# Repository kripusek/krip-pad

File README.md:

# krip-pad
This is my macro pad madwe mainly for playing osumania type games

## Features
- A 0.91 inch OLED display
- 4 keys
- An opening to see the screen, xiao rp2040 and the oled

## tolerances
should be around 0.4mm

## WIP picture of the hack pad

(yes I have a really cool mousepad)

## PCB
Here are pictures of my pcb:

| **Schematic** | **PCB** |
|---------------|---------|
|||

## CAD
I designed it using autodesk fusion

Everything fits together with 5 m3 screws and bolts

## Firmware

I wrote the firmware using qmk.

## Notes
If you want to change the mapped you can use via with the included via.json file which you can find in the firmware folder https://usevia.app/

Making this pad was fun, I got to learn qmk fusion and kicad which I can use fluently now, fusion and qmk not so much.

I have used https://github.com/hackclub/hackpad/blob/main/hackpads/cyaopad/README.md as a template for my readme

I have used https://github.com/dancarroll/qmk-bongo for the bongo animations
I have also used ai for explaining what does what in qmk, afterwards I have written the code myself and ai has helped me debug it.

## BOM
- 1 SEEEDUINO XIAO RP2040
- 4x any switch mx style
- 4x 1N4148 diodes
- 1x default 32x128 with GND-VCC-SCL-SDA pin order
- 5x same screws as orpheuspad and corresponding nuts

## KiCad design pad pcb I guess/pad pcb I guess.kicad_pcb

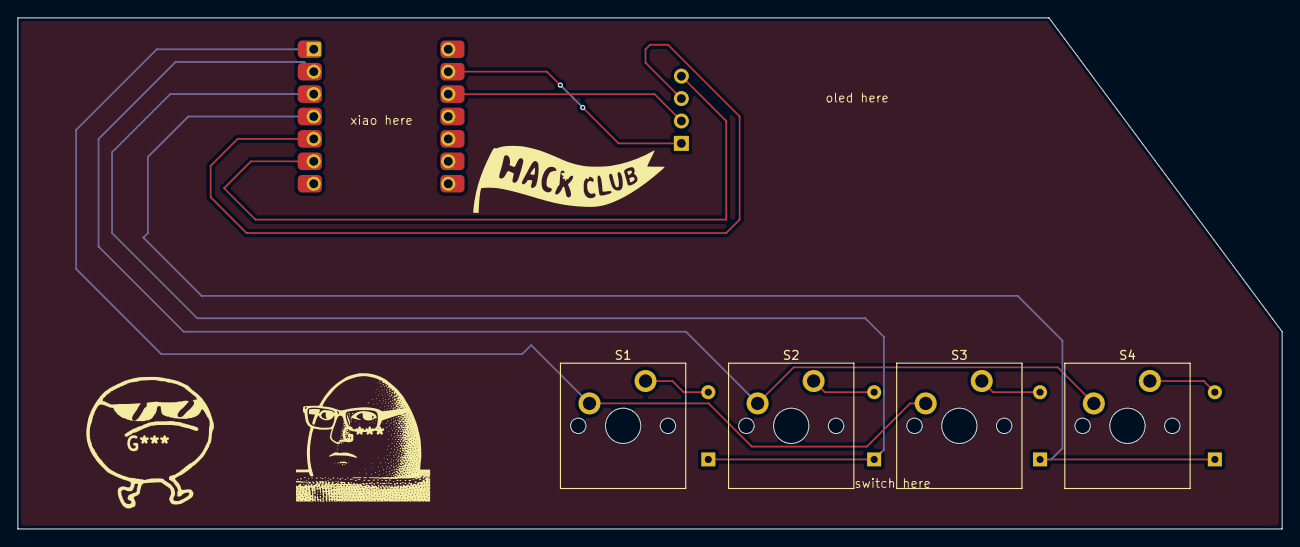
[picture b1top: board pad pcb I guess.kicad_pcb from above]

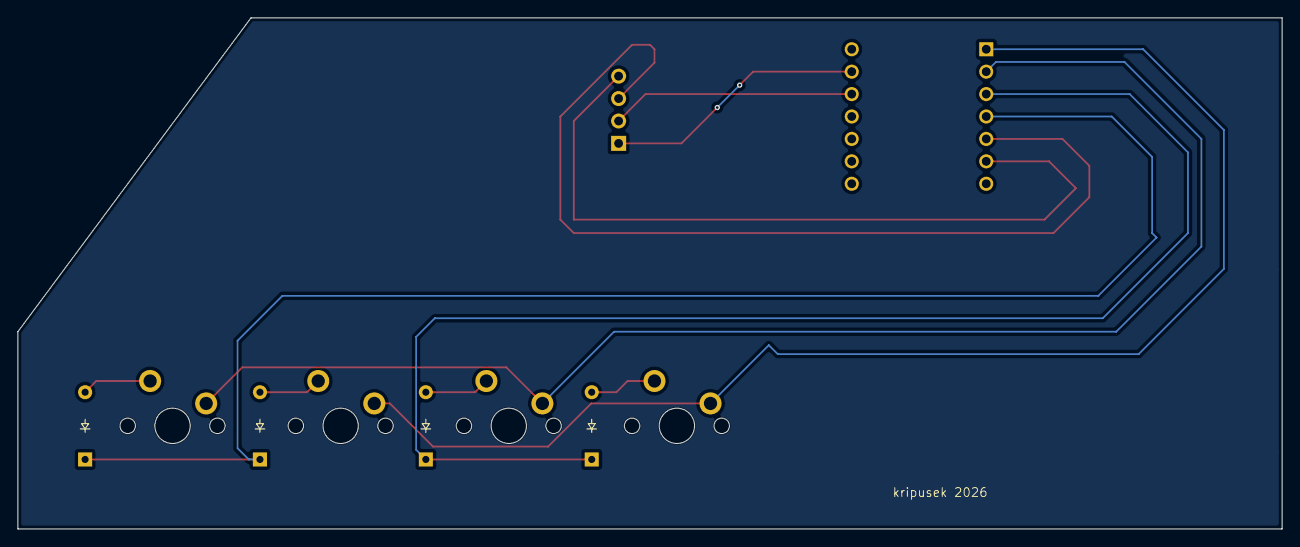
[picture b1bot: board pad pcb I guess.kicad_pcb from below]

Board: 2 copper layers, 143.3 x 57.9 mm, 10 parts (4 on the bottom side), 12 nets.

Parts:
D1, D2, D3, D4: Diode_DO-35
J1: OLED_128x32
S1, S2, S3, S4: MX_PCB_1.00u
U1: MOUDLE-SEEEDUINO-XIAO; Seeed_XIAO_RP2040

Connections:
/column 0: S1.1, S3.1, U1.1 (PA02_A0_D0)
/column 1: S2.1, S4.1, U1.2 (PA4_A1_D1)
/gnd: J1.1 (GND), U1.13 (GND)
/row 0: D1.1 (K), D2.1 (K), U1.3 (PA10_A2_D2)
/row 1: D3.1 (K), D4.1 (K), U1.4 (PA11_A3_D3)
/scl: J1.3 (SCL), U1.5 (PA8_A4_D4_SDA)
/sda: J1.4 (SDA), U1.6 (PA9_A5_D5_SCL)
/vcc: J1.2 (VCC), U1.12 (3V3)
unnamed: D1.2 (A), S1.2
unnamed: D2.2 (A), S2.2
unnamed: D3.2 (A), S3.2
unnamed: D4.2 (A), S4.2

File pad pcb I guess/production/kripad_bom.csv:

Designator,Footprint,Quantity,Value,LCSC Part #
"D1, D2, D3, D4",Diode_DO-35,4,~,
J1,OLED_128x32,1,OLED_128x32,
"S1, S2, S3, S4",MX_PCB_1.00u,4,~,
U1,Seeed_XIAO_RP2040,1,MOUDLE-SEEEDUINO-XIAO,
